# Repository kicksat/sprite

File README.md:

# sprite

A tiny open source spacecraft

# Acknowledgments

The code for Sprite, and in this repo, is derived from work by @zacmanchester, builder of KickSat and Assistant Professor of Aeronautics and Astronautics at Stanford University. Many thanks to the [KickSat project](http://kicksat.github.io/); more information can be found on the [project KickStarter](https://www.kickstarter.com/projects/251588730/kicksat-your-personal-spacecraft-in-space/posts) and the [KickSat Wiki](https://github.com/zacmanchester/kicksat/wiki).

This demo would not be possible without the assistance and guidance of [Michael Turner, @Yakushima](https://github.com/ProjectPersephone), Executive Director of [Project Persephone](http://www.projectpersephone.org/).

# License

[Creative Commons Attribution-ShareAlike 4.0 International](https://creativecommons.org/licenses/by-sa/4.0/)

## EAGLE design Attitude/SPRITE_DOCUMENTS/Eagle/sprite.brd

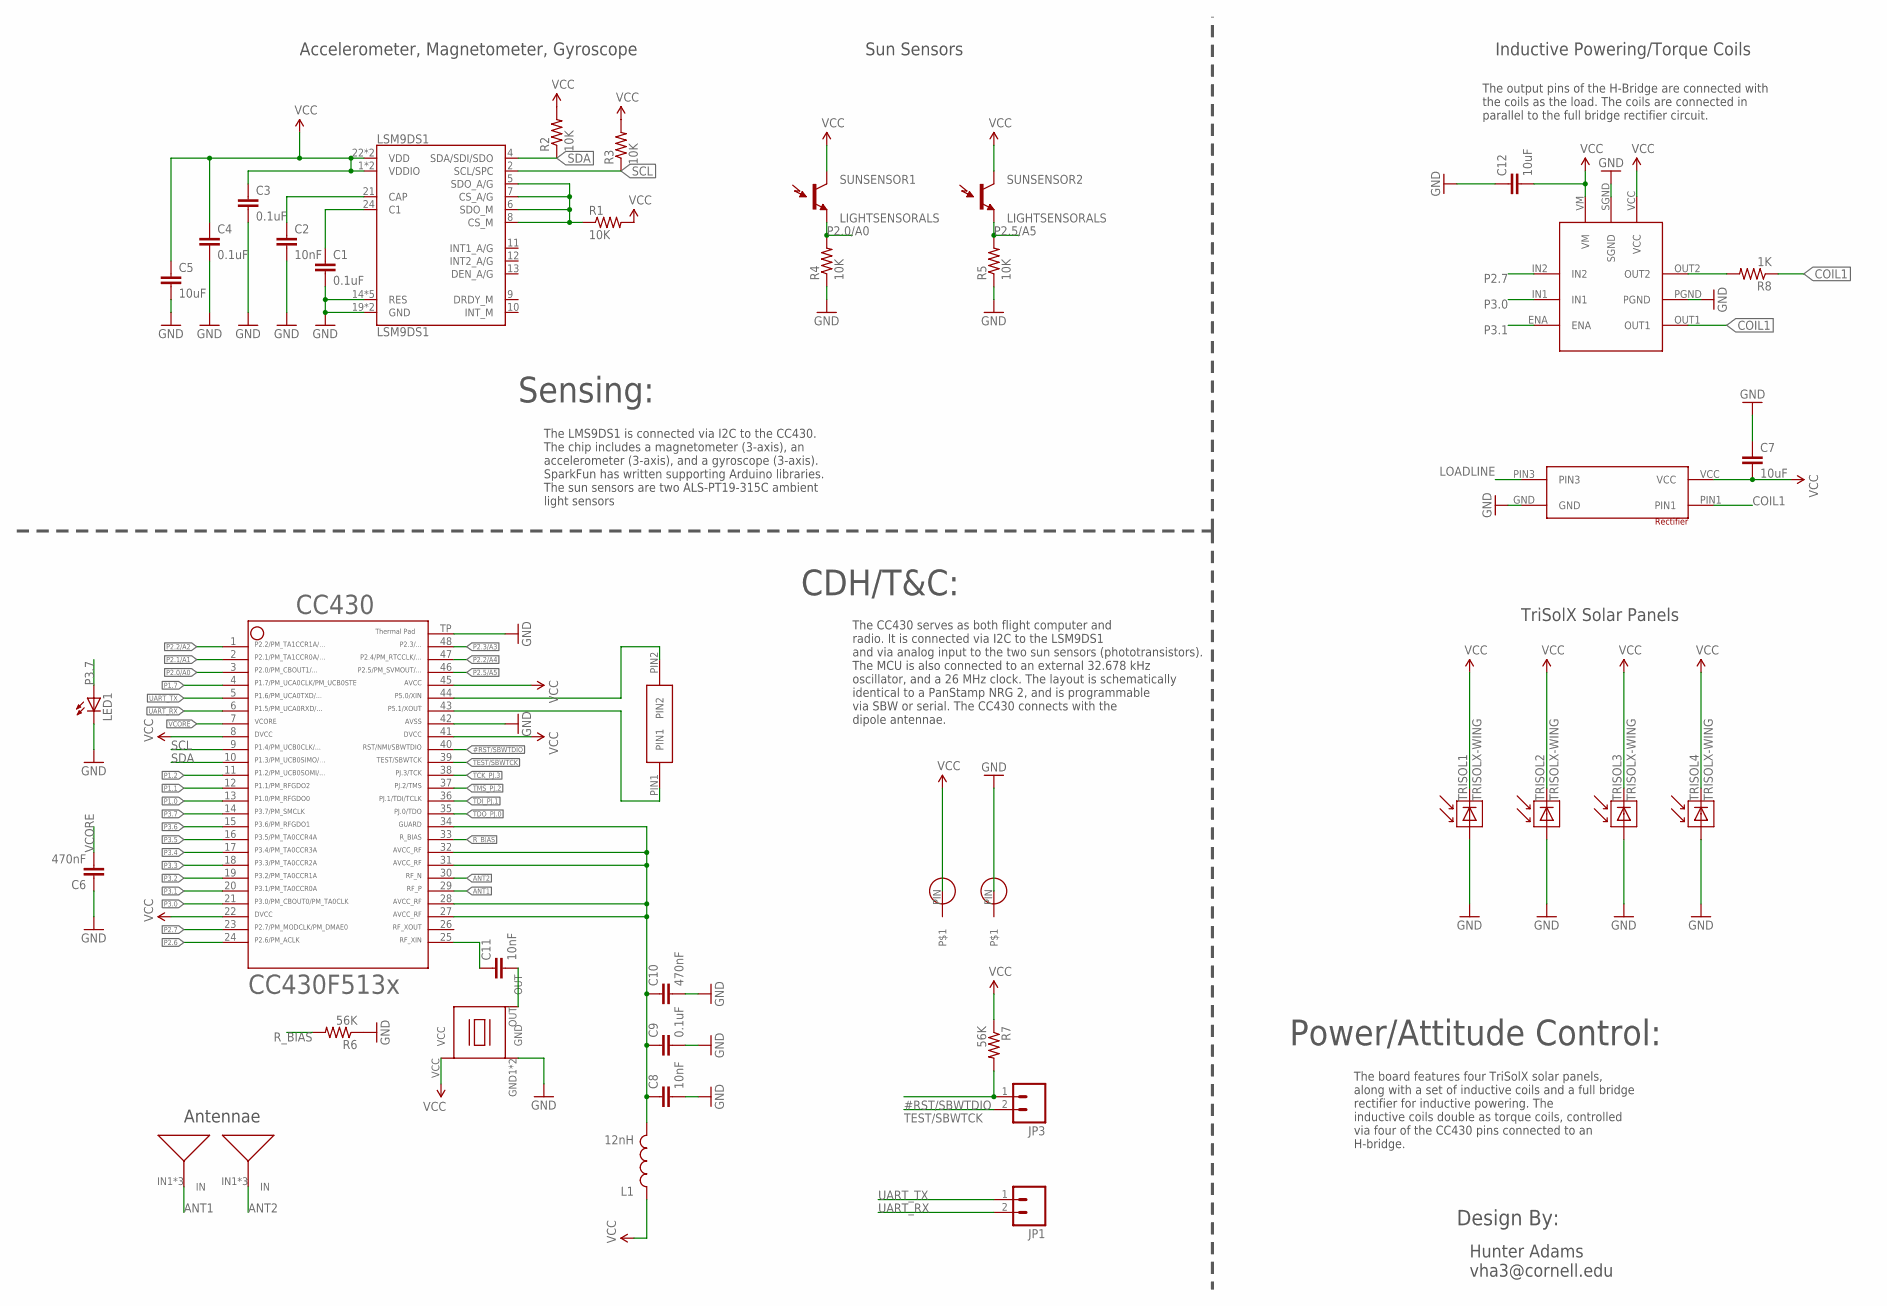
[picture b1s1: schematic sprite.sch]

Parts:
32KHZ: SPRITECRYSTALSPRITECRYSTAL; SPRITECRYSTAL
ANTENNA1, ANTENNA2: ANTENNA
C1, C3, C4, C9: 0.1uF; 0805
C2, C8, C11: 10nF; 0805
C5, C7, C12: 10uF; 0805
C6, C10: 470nF; 0805
CC430: CC430F513X---RGZ48; RGZ48
GNDPIN: SPRITE_PIN
H-BRIDGE: LV8417CS
JP1, JP3: M02PTH; 1X02
L1: 12nH; C0402
LED1: LED0603; LED-0603
LSM9DS1: LSM9DS1; LGA24-8X4
R1, R2, R3, R4, R5: 10K; 0805
R6, R7: 56K; 0805
R8: 1K; 0805
RECTIFIER: NSR1030QMUTAG
SUNSENSOR1, SUNSENSOR2: LIGHTSENSORALS; ALS-PT19
TRISOL1, TRISOL2, TRISOL3, TRISOL4: TRISOLX-WING; TRISOLX-T01
TXCO: TCXO_7Z; TXC_7Z
VCCPIN: SPRITE_PIN

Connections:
#RST/SBWTDIO: CC430.40, JP3.1, R7.2
ANT1: ANTENNA1.IN1, ANTENNA1.IN2, ANTENNA1.IN3, CC430.29
ANT2: ANTENNA2.IN1, ANTENNA2.IN2, ANTENNA2.IN3, CC430.30
COIL1: H-BRIDGE.OUT1, R8.1, RECTIFIER.PIN1
GND: C1.2, C2.2, C3.2, C4.2, C5.2, C6.1, C7.1, C8.2, C9.2, C10.2, C12.1, CC430.42, CC430.TP (49), GNDPIN.PIN, H-BRIDGE.PGND, H-BRIDGE.SGND, LED1.C, LSM9DS1.14 (RES), LSM9DS1.15 (RES), LSM9DS1.16 (RES), LSM9DS1.17 (RES), LSM9DS1.18 (RES), LSM9DS1.19 (GND), LSM9DS1.20 (GND), R4.1, R5.1, R6.1, RECTIFIER.GND, TRISOL1.P$3 (A), TRISOL2.P$3 (A), TRISOL3.P$3 (A), TRISOL4.P$3 (A), TXCO.GND1 (GND), TXCO.GND2 (GND)
GUARD: C8.1, C9.1, C10.1, CC430.27, CC430.28, CC430.31, CC430.32, CC430.34, L1.2
LOADLINE: H-BRIDGE.OUT2, R8.2, RECTIFIER.PIN3
unnamed: C1.1, LSM9DS1.24 (C1)
unnamed: C2.1, LSM9DS1.21 (CAP)
unnamed: LSM9DS1.5 (SDO_A/G), LSM9DS1.6 (SDO_M), LSM9DS1.7 (CS_A/G), LSM9DS1.8 (CS_M), R1.1
unnamed: C11.1, CC430.25
unnamed: C11.2, TXCO.OUT
unnamed: 32KHZ.PIN2, CC430.44
unnamed: 32KHZ.PIN1, CC430.43
P1.0: CC430.13
P1.1: CC430.12
P1.2: CC430.11
P1.7: CC430.4
P2.0/A0: CC430.3, R4.2, SUNSENSOR1.E (E1)
P2.1/A1: CC430.2
P2.2/A2: CC430.1
P2.2/A4: CC430.47
P2.3/A3: CC430.48
P2.5/A5: CC430.46, R5.2, SUNSENSOR2.E (E1)
P2.6: CC430.24
P2.7: CC430.23, H-BRIDGE.IN2
P3.0: CC430.21, H-BRIDGE.IN1
P3.1: CC430.20, H-BRIDGE.ENA
P3.2: CC430.19
P3.3: CC430.18
P3.4: CC430.17
P3.5: CC430.16
P3.6: CC430.15
P3.7: CC430.14, LED1.A
R_BIAS: CC430.33, R6.2
SCL: CC430.9, LSM9DS1.2 (SCL/SPC), R3.1
SDA: CC430.10, LSM9DS1.4 (SDA/SDI/SDO), R2.1
TCK_PJ.3: CC430.38
TDI_PJ.1: CC430.36
TDO_PJ.0: CC430.35
TEST/SBWTCK: CC430.39, JP3.2
TMS_PJ.2: CC430.37
UART_RX: CC430.6, JP1.2
UART_TX: CC430.5, JP1.1
VCC: C3.1, C4.1, C5.1, C7.2, C12.2, CC430.8, CC430.22, CC430.41, CC430.45, H-BRIDGE.VCC, H-BRIDGE.VM, L1.1, LSM9DS1.1 (VDDIO), LSM9DS1.3 (VDDIO), LSM9DS1.22 (VDD), LSM9DS1.23 (VDD), R1.2, R2.2, R3.2, R7.1, RECTIFIER.VCC, SUNSENSOR1.C (C1), SUNSENSOR2.C (C1), TRISOL1.P$2 (C), TRISOL2.P$2 (C), TRISOL3.P$2 (C), TRISOL4.P$2 (C), TXCO.VCC, VCCPIN.PIN
VCORE: C6.2, CC430.7

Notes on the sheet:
Accelerometer, Magnetometer, Gyroscope
Sun Sensors
The LMS9DS1 is connected via I2C to the CC430. The chip includes a magnetometer (3-axis), an accelerometer (3-axis), and a gyroscope (3-axis). SparkFun has written supporting Arduino libraries. The sun sensors are two ALS-PT19-315C ambient light sensors
Sensing:
CDH/T&C:
The CC430 serves as both flight computer and radio. It is connected via I2C to the LSM9DS1 and via analog input to the two sun sensors (phototransistors). The MCU is also connected to an external 32.678 kHz oscillator, and a 26 MHz clock. The layout is schematically identical to a PanStamp NRG 2, a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
Power/Attitude Control:
The board features four TriSolX solar panels, along with a set of inductive coils and a full bridge rectifier for inductive powering. The inductive coils double as torque coils, controlled via four of the CC430 pins connected to an H-bridge.
Antennae
TriSolX Solar Panels
Inductive Powering/Torque Coils
Hunter Adams vha3@cornell.edu
Design By:
The output pins of the H-Bridge are connected with the coils as the load. The coils are connected in parallel to the full bridge rectifier circuit.

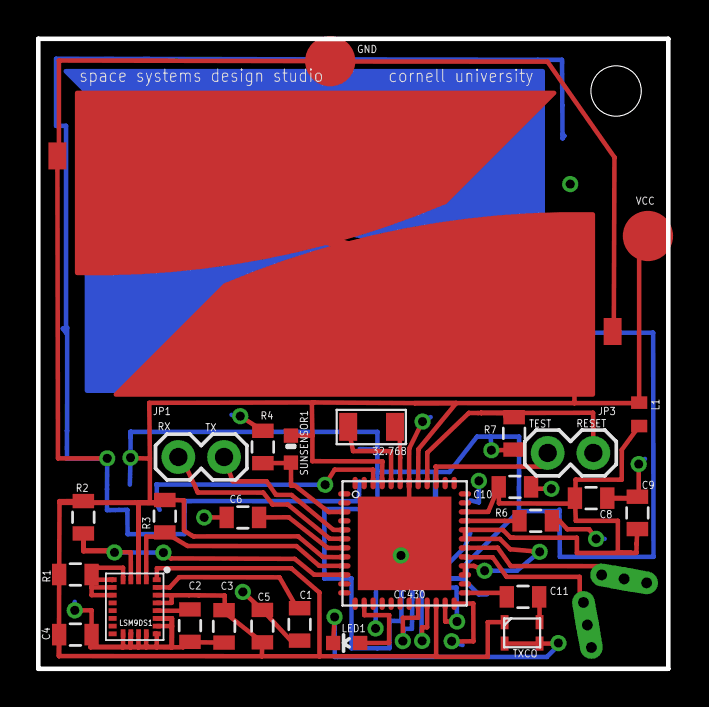
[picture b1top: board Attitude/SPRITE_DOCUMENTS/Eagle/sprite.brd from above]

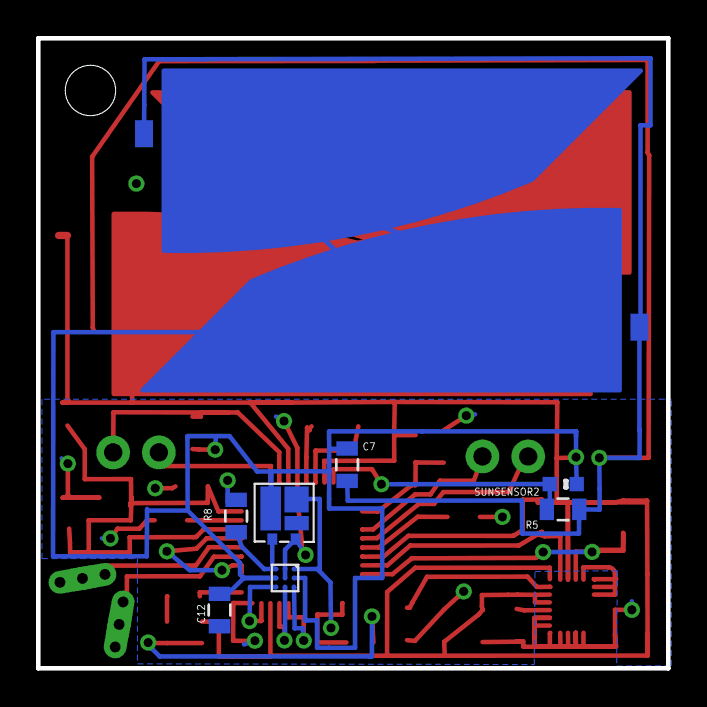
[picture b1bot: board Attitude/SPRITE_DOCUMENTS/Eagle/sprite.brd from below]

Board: 4 copper layers, 35.0 x 35.0 mm, 40 parts (9 on the bottom side), 28 nets.

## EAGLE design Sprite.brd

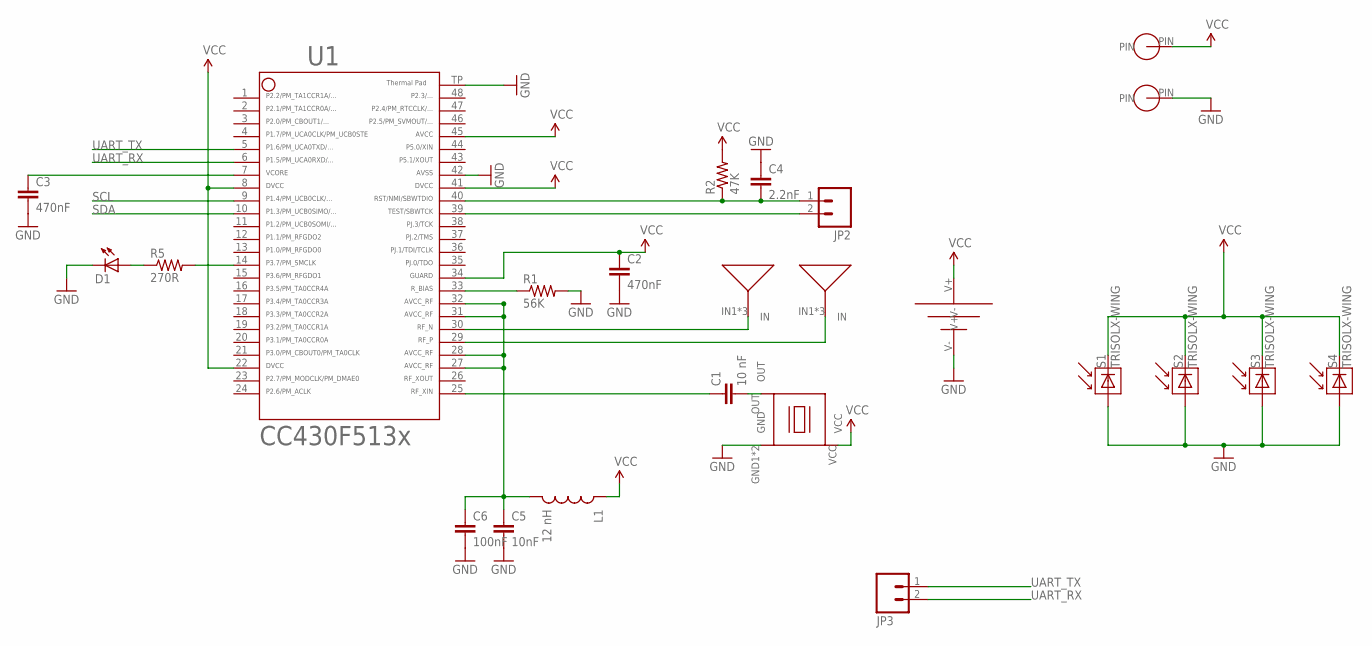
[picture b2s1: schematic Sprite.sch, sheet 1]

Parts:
ANT-N: ANTENNA
ANT-P: ANTENNA
C1: 10 nF; 0603-CAP
C2, C3: 470nF; 0603-CAP
C4: 2.2nF; 0603-CAP
C5: 10nF; 0603-CAP
C6: 100nF; 0603-CAP
D1: LED0603; LED-0603
JP2, JP3: M02PTH; 1X02
L1: 12 nH; 0603
P1, P2: SPRITE_PIN
R1: 56K; 0603-RES
R2: 47K; 0603-RES
R5: 270R; 0603-RES
S1, S2, S3, S4: TRISOLX-WING; TRISOLX-T01
U1: CC430F5137; RGZ48
U$1: UMAC
X1: TCXO_7Z; TXC_7Z

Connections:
GND: C2.2, C3.2, C4.1, C5.2, C6.2, D1.C, P2.PIN, R1.2, S1.P$3 (A), S2.P$3 (A), S3.P$3 (A), S4.P$3 (A), U1.42, U1.TP (49), U$1.V-, X1.GND1 (GND), X1.GND2 (GND)
unnamed: C1.1, U1.25
unnamed: R5.2, U1.14
unnamed: R1.1, U1.33
unnamed: C3.1, U1.7
unnamed: D1.A, R5.1
unnamed: C1.2, X1.OUT
RFN: ANT-N.IN1, ANT-N.IN2, ANT-N.IN3, U1.30
RFP: ANT-P.IN1, ANT-P.IN2, ANT-P.IN3, U1.29
RST: C4.2, JP2.1, R2.1, U1.40
SCL: U1.9
SDA: U1.10
TEST: JP2.2, U1.39
UART_RX: JP3.2, U1.6
UART_TX: JP3.1, U1.5
VCC: C2.1, L1.1, P1.PIN, R2.2, S1.P$2 (C), S2.P$2 (C), S3.P$2 (C), S4.P$2 (C), U1.8, U1.22, U1.34, U1.41, U1.45, U$1.V+, X1.VCC
VCCRF: C5.1, C6.1, L1.2, U1.27, U1.28, U1.31, U1.32

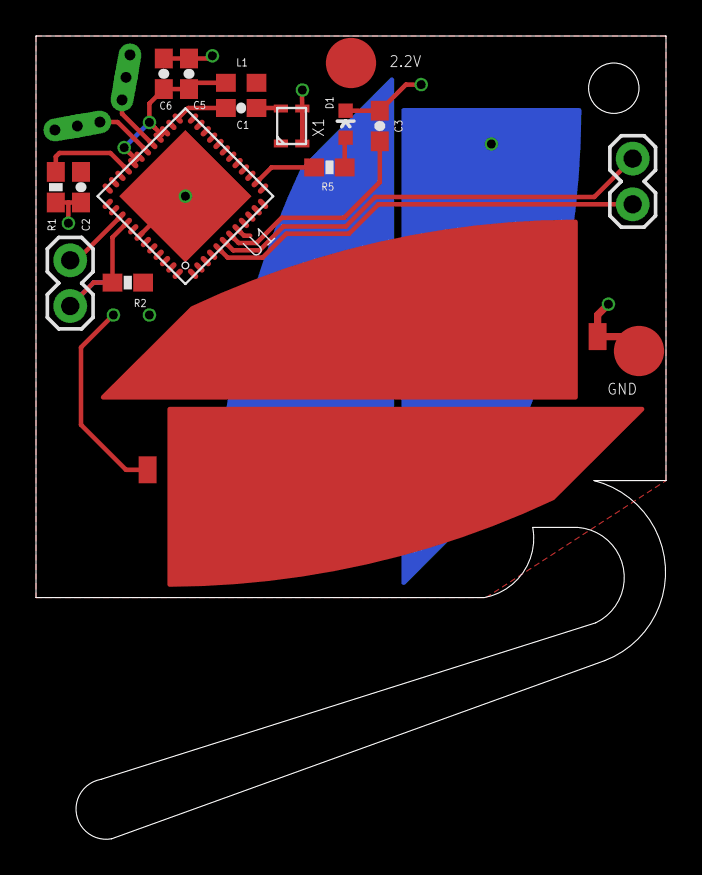
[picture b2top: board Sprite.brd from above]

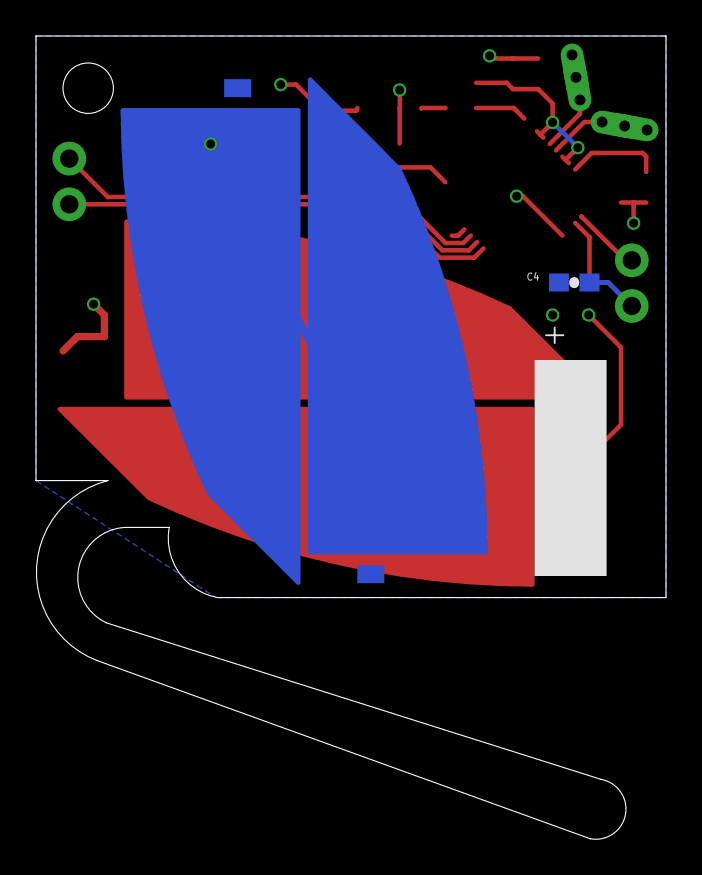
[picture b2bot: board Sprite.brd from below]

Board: 2 copper layers, 35.0 x 44.6 mm, 24 parts (4 on the bottom side), 15 nets.

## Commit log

2014-06-02 Initial move
2014-07-23 Added test code
2014-07-23 Some edits to compas demo
2014-07-24 Updated GyroDemo
2016-04-19 Fixed inconsistency between .brd and .sch
2016-04-19 Added .gitignore
2016-04-24 Adding IMU + TrisolX parts
2016-04-27 Rolled my own motor driver
2016-04-27 Revert "Rolled my own motor driver"
    This reverts commit 8d15a71afd97314b3e3036af91b9c243df8797f7.
2016-05-12 Sprite layout with TrisolX
2016-05-12 Finished new layout
2016-05-13 Swapped pins
2016-05-20 Updated files for fab
2016-05-20 Added Centroid data
2016-05-23 Added fab readme + solar cell picture
2016-05-26 Fixed part numbering (duplicate R5)
2016-06-01 Update TrisolX footprint
2018-01-23 New outline with board spring
2018-01-30 moved solar cells + antenna on new board
2018-02-13 New sprite with spring
2018-04-19 Added murata UMAC battery
2018-06-18 Moved files inessential for demo to S_F_F folder
2018-06-18 Moved inessential extra files+documentation to SFF
2018-06-18 Restoring prog_files
2018-06-18 Restoring programmer files -- not deleting them
2018-06-18 Updated .gitignore to include full repo
2018-06-18 Gitignore returned to normal
2018-07-20 All things sprite compiled
2018-07-20 Set theme jekyll-theme-midnight
2018-10-08 Revert "All things sprite compiled"
    This reverts commit 57d04d4f7100c9d78c9e83d719de1b6c8f8ca531.
2018-10-19 Updated .gitignore

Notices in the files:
parts and their libraries:
SparkFun-Sensors: Licensing: Creative Commons ShareAlike 4.0 International - https://creativecommons.org/licenses/by-sa/4.0
SparkFun: Licensing: CC v3.0 Share-Alike You are welcome to use this library for commercial purposes.
